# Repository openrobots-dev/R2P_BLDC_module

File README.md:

R2P_BLDC_module
===============

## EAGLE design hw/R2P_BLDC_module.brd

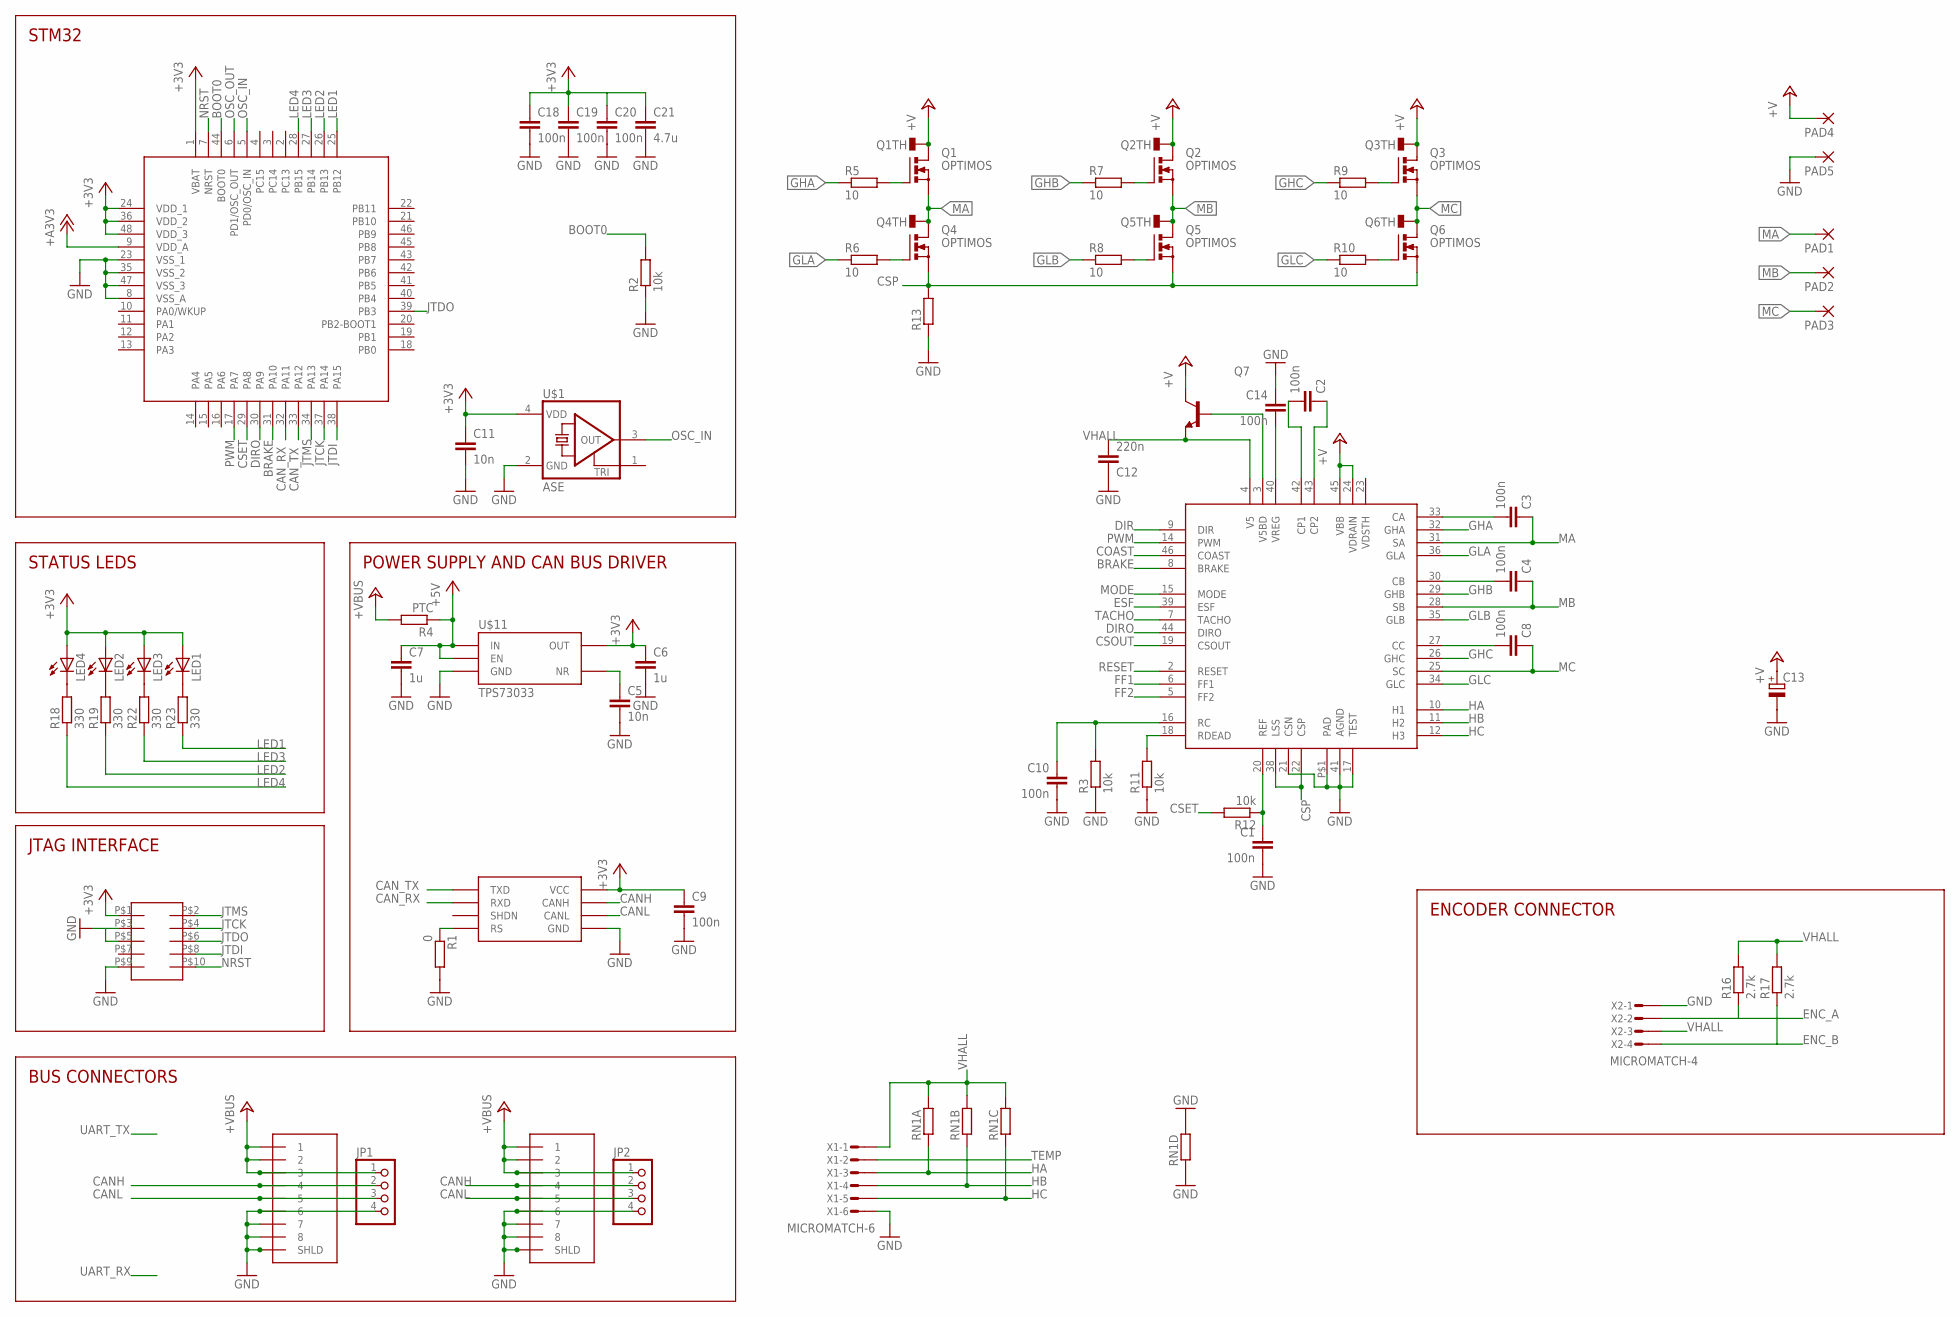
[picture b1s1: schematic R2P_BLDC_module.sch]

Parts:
1, 2: RJ45-43860; 0438600010
C1, C2, C3, C4, C8, C9, C10, C14, C18, C19, C20: 100n; C0603
C5, C11: 10n; C0603
C6, C7: 1u; C0603
C12: 220n; C0603
C13: CPOL-EUE35-12AXIAL; E35-12
C21: 4.7u; C0805
JP1, JP2: PINHD-1X4; 1X04
LED1, LED2, LED3, LED4: LEDCHIPLED_0805; CHIPLED_0805
PAD1, PAD2, PAD3, PAD4, PAD5: 3,81/1,4
Q1, Q2, Q3, Q4, Q5, Q6: OPTIMOS; PG-TDSON-8
Q7: TRANSISTOR_BJT_NPN-SOT-23-BCE; SOT-23
R1: 0; R0603
R2, R3, R11, R12: 10k; R0603
R4: PTC; R0805
R5, R6, R7, R8, R9, R10: 10; R0603
R13: R-EU_R2512; R2512
R16, R17: 2.7k; R0603
R18, R19, R22, R23: 330; R0603
RN1: RESISTOR_ARRAY_4; RN8P-4R-CRA06S
SOT1: MAX3051; SOT23-8L
U1: STM32F103CX; LQFP48
U$1: ASE
U$2: A3930; TQFP48
U$4: FTSH-105
U$11: TPS73033; SOT23-5L
X1: MICROMATCH-6
X2: MICROMATCH-4

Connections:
+3V3: C6.1, C9.1, C11.1, C18.1, C19.1, C20.1, C21.1, LED1.A, LED2.A, LED3.A, LED4.A, SOT1.P$3 (VCC), U1.1 (VBAT), U1.24 (VDD_1), U1.36 (VDD_2), U1.48 (VDD_3), U$1.4 (VDD), U$4.P$1, U$11.5 (OUT)
+5V: C7.1, R4.1, U$11.1 (IN), U$11.3 (EN)
+A3V3: U1.9 (VDD_A)
+V: C13.+, PAD4.1, Q1.5 (D), Q1.6 (D), Q1.7 (D), Q1.8 (D), Q1.TH, Q2.5 (D), Q2.6 (D), Q2.7 (D), Q2.8 (D), Q2.TH, Q3.5 (D), Q3.6 (D), Q3.7 (D), Q3.8 (D), Q3.TH, Q7.2 (C), U$2.24 (VDRAIN), U$2.45 (VBB)
+VBUS: 1.P$1 (1), 1.P$2 (2), 1.P$3 (3), 2.P$1 (1), 2.P$2 (2), 2.P$3 (3), JP1.1, JP2.1, R4.2
BOOT0: R2.2, U1.44 (BOOT0)
BRAKE: U1.31 (PA10), U$2.8 (BRAKE)
CANH: 1.P$4 (4), 2.P$4 (4), JP1.2, JP2.2, SOT1.P$7 (CANH)
CANL: 1.P$5 (5), 2.P$5 (5), JP1.3, JP2.3, SOT1.P$6 (CANL)
CAN_RX: SOT1.P$4 (RXD), U1.32 (PA11)
CAN_TX: SOT1.P$1 (TXD), U1.33 (PA12)
COAST: U$2.46 (COAST)
CSET: R12.2, U1.29 (PA8)
CSOUT: U$2.19 (CSOUT)
CSP: Q4.1 (S), Q4.2 (S), Q4.3 (S), Q5.1 (S), Q5.2 (S), Q5.3 (S), Q6.1 (S), Q6.2 (S), Q6.3 (S), R13.2, U$2.22 (CSP), U$2.38 (LSS)
DIR: U$2.9 (DIR)
DIRO: U1.30 (PA9), U$2.44 (DIRO)
ENC_A: R16.1, X2.2
ENC_B: R17.1, X2.4
ESF: U$2.39 (ESF)
FF1: U$2.6 (FF1)
FF2: U$2.5 (FF2)
GHA: R5.1, U$2.32 (GHA)
GHB: R7.1, U$2.29 (GHB)
GHC: R9.1, U$2.26 (GHC)
GLA: R6.1, U$2.36 (GLA)
GLB: R8.1, U$2.35 (GLB)
GLC: R10.1, U$2.34 (GLC)
GND: 1.P$6 (6), 1.P$7 (7), 1.P$8 (8), 1.P$9 (SHLD), 1.P$10, 2.P$6 (6), 2.P$7 (7), 2.P$8 (8), 2.P$9 (SHLD), 2.P$10, C1.2, C5.2, C6.2, C7.2, C9.2, C10.2, C11.2, C12.1, C13.-, C14.1, C18.2, C19.2, C20.2, C21.2, JP1.4, JP2.4, PAD5.1, R1.2, R2.1, R3.1, R11.1, R13.1, RN1.4 (1), RN1.5 (2), SOT1.P$2 (GND), U1.8 (VSS_A), U1.23 (VSS_1), U1.35 (VSS_2), U1.47 (VSS_3), U$1.2 (GND), U$2.17 (TEST), U$2.21 (CSN), U$2.41 (AGND), U$2.P$1 (PAD), U$4.P$3, U$4.P$9, U$11.2 (GND), X1.6, X2.1
HA: RN1.1, U$2.10 (H1), X1.3
HB: RN1.2 (1), U$2.11 (H2), X1.4
HC: RN1.3 (1), U$2.12 (H3), X1.5
JTCK: U1.37 (PA14), U$4.P$4
JTDI: U1.38 (PA15), U$4.P$8
JTDO: U1.39 (PB3), U$4.P$6
JTMS: U1.34 (PA13), U$4.P$2
LED1: R23.1, U1.25 (PB12)
LED2: R19.1, U1.26 (PB13)
LED3: R22.1, U1.27 (PB14)
LED4: R18.1, U1.28 (PB15)
MA: C3.1, PAD1.1, Q1.1 (S), Q1.2 (S), Q1.3 (S), Q4.5 (D), Q4.6 (D), Q4.7 (D), Q4.8 (D), Q4.TH, U$2.31 (SA)
MB: C4.1, PAD2.1, Q2.1 (S), Q2.2 (S), Q2.3 (S), Q5.5 (D), Q5.6 (D), Q5.7 (D), Q5.8 (D), Q5.TH, U$2.28 (SB)
MC: C8.1, PAD3.1, Q3.1 (S), Q3.2 (S), Q3.3 (S), Q6.5 (D), Q6.6 (D), Q6.7 (D), Q6.8 (D), Q6.TH, U$2.25 (SC)
MODE: U$2.15 (MODE)
unnamed: R1.1, SOT1.P$8 (RS)
unnamed: C3.2, U$2.33 (CA)
unnamed: C5.1, U$11.4 (NR)
unnamed: C2.2, U$2.42 (CP1)
unnamed: R11.2, U$2.18 (RDEAD)
unnamed: Q1.4 (G), R5.2
unnamed: Q4.4 (G), R6.2
unnamed: Q2.4 (G), R7.2
unnamed: C2.1, U$2.43 (CP2)
unnamed: Q5.4 (G), R8.2
unnamed: Q3.4 (G), R9.2
unnamed: Q6.4 (G), R10.2
unnamed: C4.2, U$2.30 (CB)
unnamed: LED4.C, R18.2
unnamed: C1.1, R12.1, U$2.20 (REF)
unnamed: C10.1, R3.2, U$2.16 (RC)
unnamed: LED2.C, R19.2
unnamed: C8.2, U$2.27 (CC)
unnamed: LED3.C, R22.2
unnamed: C14.2, U$2.40 (VREG)
unnamed: LED1.C, R23.2
unnamed: Q7.1 (B), U$2.3 (V5BD)
NRST: U1.7 (NRST), U$4.P$10
OSC_IN: U1.5 (PD0/OSC_IN), U$1.3 (OUT)
OSC_OUT: U1.6 (PD1/OSC_OUT)
PWM: U1.17 (PA7), U$2.14 (PWM)
RESET: U$2.2 (RESET)
TACHO: U$2.7 (TACHO)
TEMP: X1.2
VHALL: C12.2, Q7.3 (E), R16.2, R17.2, RN1.6 (2), RN1.7 (2), RN1.8 (2), U$2.4 (V5), X1.1, X2.3

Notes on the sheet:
STM32
POWER SUPPLY AND CAN BUS DRIVER
STATUS LEDS
JTAG INTERFACE
BUS CONNECTORS
ENCODER CONNECTOR

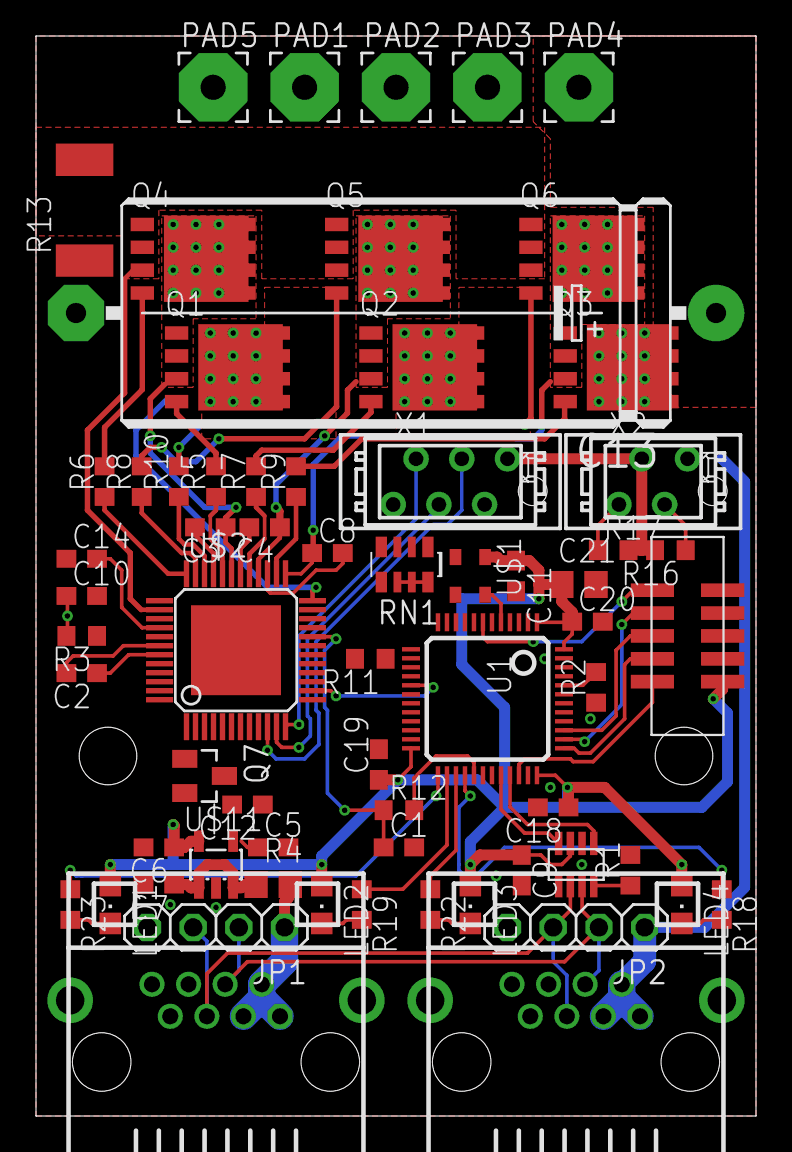
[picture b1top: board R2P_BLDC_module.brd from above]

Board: 2 copper layers, 40.0 x 60.0 mm, 66 parts (0 on the bottom side), 62 nets.

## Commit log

2013-06-07 Working on layout
2013-06-13 H-bridge layout almost done
2013-06-13 H-bridge layout complete
2013-10-24 hall connector to be placed
2013-10-24 started layout
2013-10-24 added A3930 datasheet
